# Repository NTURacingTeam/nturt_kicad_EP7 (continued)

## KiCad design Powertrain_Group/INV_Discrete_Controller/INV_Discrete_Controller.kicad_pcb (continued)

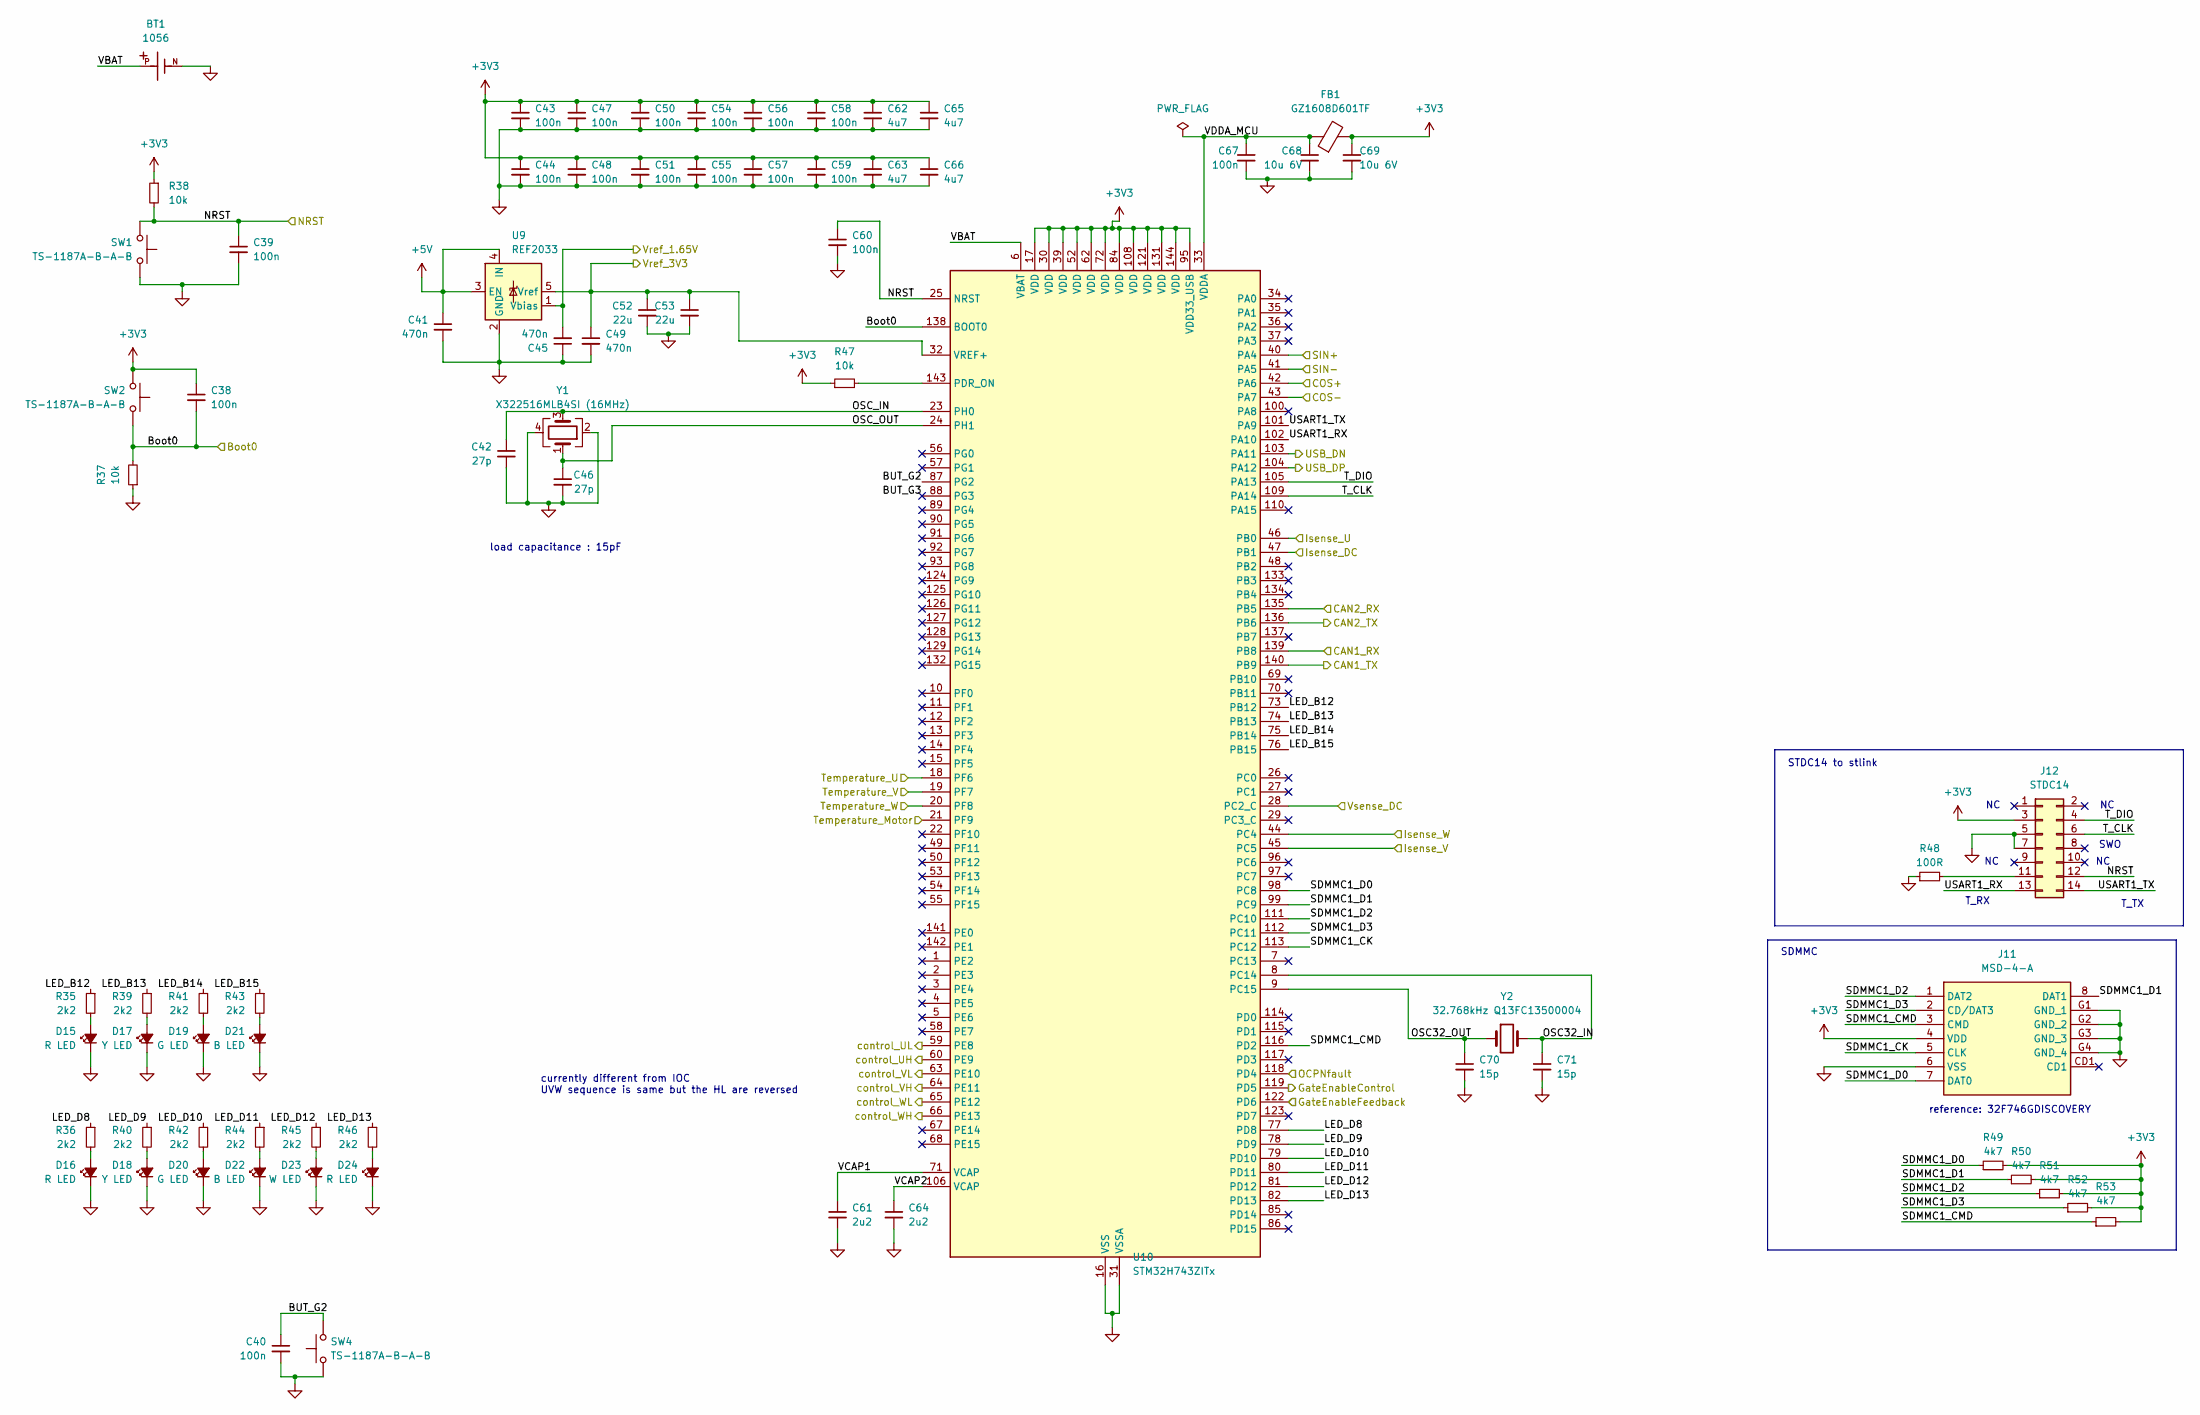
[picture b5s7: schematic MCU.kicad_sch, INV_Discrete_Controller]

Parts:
BT1: 1056; BAT_1056; PARTREV D
C38, C39, C40, C43, C44, C47, C48, C50, C51, C54, C55, C56, C57, C58, C59, C60, C67: 100n; C_0402_1005Metric
C41, C45, C49: 470n; C_0603_1608Metric
C42, C46: 27p; C_0402_1005Metric
C52, C53: 22u; C_0805_2012Metric
C61, C64: 2u2; C_0402_1005Metric
C62, C63, C65, C66: 4u7; C_0402_1005Metric
C68, C69: 10u 6V; C_0402_1005Metric
C70, C71: 15p; C_0402_1005Metric
D15, D16, D24: R LED; LED_0603_1608Metric
D17, D18: Y LED; LED_0603_1608Metric
D19, D20: G LED; LED_0603_1608Metric
D21, D22: B LED; LED_0603_1608Metric
D23: W LED; LED_0603_1608Metric
FB1: GZ1608D601TF; C_0603_1608Metric
J11: MSD-4-A; MSD4A; Mouser Part Number 179-MSD-4-A
J12: STDC14; box_header_14P_pitch1.27
R35, R36, R39, R40, R41, R42, R43, R44, R45, R46: 2k2; R_0402_1005Metric
R37, R38, R47: 10k; R_0402_1005Metric
R48: 100R; R_0402_1005Metric
R49, R50, R51, R52, R53: 4k7; R_0402_1005Metric
SW1, SW2, SW4: TS-1187A-B-A-B; SW_SPST_TL3342
U9: REF2033; SOT-23-5
U10: STM32H743ZITx; LQFP-144_20x20mm_P0.5mm
Y1: X322516MLB4SI (16MHz); Crystal_SMD_3225-4Pin_3.2x2.5mm
Y2: 32.768kHz Q13FC13500004; Crystal_SMD_3215-2Pin_3.2x1.5mm

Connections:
+3V3: C38.1, C43.1, C44.1, C47.1, C48.1, C50.1, C51.1, C54.1, C55.1, C56.1, C57.1, C58.1, C59.1, C62.1, C63.1, C65.1, C66.1, C69.1, FB1.2, J11.4 (VDD), J12.3, R38.1, R47.1, R49.2, R50.2, R51.2, R52.2, R53.2, SW2.2, U10.17 (VDD), U10.30 (VDD), U10.39 (VDD), U10.52 (VDD), U10.62 (VDD), U10.72 (VDD), U10.84 (VDD), U10.95 (VDD33_USB), U10.108 (VDD), U10.121 (VDD), U10.131 (VDD), U10.144 (VDD); also elsewhere on the board
+5V: C41.1, U9.3 (EN), U9.4 (IN); also elsewhere on the board
/EncoderDifVconverter/cos+3V3_out: U10.42 (PA6); also elsewhere on the board
/EncoderDifVconverter/cos-3V3_out: U10.43 (PA7); also elsewhere on the board
/EncoderDifVconverter/sin+3V3_out: U10.40 (PA4); also elsewhere on the board
/EncoderDifVconverter/sin-3V3_out: U10.41 (PA5); also elsewhere on the board
/GATE_EN: U10.122 (PD6); also elsewhere on the board
/GATE_ENC: U10.119 (PD5); also elsewhere on the board
/Isense&motT_OCP&OTP/Isense_DC: U10.47 (PB1); also elsewhere on the board
/Isense&motT_OCP&OTP/Isense_U: U10.46 (PB0); also elsewhere on the board
/Isense&motT_OCP&OTP/Isense_V: U10.45 (PC5); also elsewhere on the board
/Isense&motT_OCP&OTP/Isense_W: U10.44 (PC4); also elsewhere on the board
/Isense&motT_OCP&OTP/T_U: U10.18 (PF6); also elsewhere on the board
/Isense&motT_OCP&OTP/T_V: U10.19 (PF7); also elsewhere on the board
/Isense&motT_OCP&OTP/T_W: U10.20 (PF8); also elsewhere on the board
/Isense&motT_OCP&OTP/Temp_mot: U10.21 (PF9); also elsewhere on the board
/Isense&motT_OCP&OTP/Vref_1.65V: C45.2, U9.1 (Vbias); also elsewhere on the board
/Isense&motT_OCP&OTP/Vref_3V3: C49.1, C52.1, C53.1, U9.5 (Vref), U10.32 (VREF+)
/MCU/BUT_G2: C40.1, SW4.2, U10.87 (PG2)
/MCU/BUT_G3: U10.88 (PG3)
/MCU/Boot0: C38.2, R37.2, SW2.1, U10.138 (BOOT0); also elsewhere on the board
/MCU/CAN1_RX: U10.139 (PB8); also elsewhere on the board
/MCU/CAN1_TX: U10.140 (PB9); also elsewhere on the board
/MCU/CAN2_RX: U10.135 (PB5); also elsewhere on the board
/MCU/CAN2_TX: U10.136 (PB6); also elsewhere on the board
/MCU/LED_B12: R35.1, U10.73 (PB12)
/MCU/LED_B13: R39.1, U10.74 (PB13)
/MCU/LED_B14: R41.1, U10.75 (PB14)
/MCU/LED_B15: R43.1, U10.76 (PB15)
/MCU/LED_D8: R36.1, U10.77 (PD8)
/MCU/LED_D9: R40.1, U10.78 (PD9)
/MCU/LED_D10: R42.1, U10.79 (PD10)
/MCU/LED_D11: R44.1, U10.80 (PD11)
/MCU/LED_D12: R45.1, U10.81 (PD12)
/MCU/LED_D13: R46.1, U10.82 (PD13)
/MCU/NRST: C39.1, C60.1, J12.12, R38.2, SW1.2, U10.25 (NRST); also elsewhere on the board
/MCU/OSC32_IN: C71.1, U10.8 (PC14), Y2.2
/MCU/OSC32_OUT: C70.1, U10.9 (PC15), Y2.1
/MCU/OSC_IN: C42.1, U10.23 (PH0), Y1.3
/MCU/OSC_OUT: C46.1, U10.24 (PH1), Y1.1
/MCU/SDMMC1_CK: J11.5 (CLK), U10.113 (PC12)
/MCU/SDMMC1_CMD: J11.3 (CMD), R53.1, U10.116 (PD2)
/MCU/SDMMC1_D0: J11.7 (DAT0), R49.1, U10.98 (PC8)
/MCU/SDMMC1_D1: J11.8 (DAT1), R50.1, U10.99 (PC9)
/MCU/SDMMC1_D2: J11.1 (DAT2), R51.1, U10.111 (PC10)
/MCU/SDMMC1_D3: J11.2 (CD/DAT3), R52.1, U10.112 (PC11)
/MCU/T_CLK: J12.6, U10.109 (PA14)
/MCU/T_DIO: J12.4, U10.105 (PA13)
/MCU/USART1_RX: J12.13, U10.102 (PA10)
/MCU/USART1_TX: J12.14, U10.101 (PA9)
/MCU/USB_DN: U10.103 (PA11); also elsewhere on the board
/MCU/USB_DP: U10.104 (PA12); also elsewhere on the board
/MCU/VBAT: BT1.P, U10.6 (VBAT)
/MCU/VCAP1: C61.1, U10.71 (VCAP)
/MCU/VCAP2: C64.1, U10.106 (VCAP)
/MCU/VDDA_MCU: C67.1, C68.1, FB1.1, U10.33 (VDDA)
/MCU/Vsense_DC: U10.28 (PC2_C); also elsewhere on the board
/OCPFLTN: U10.118 (PD4); also elsewhere on the board
/UH: U10.60 (PE9); also elsewhere on the board
/UL: U10.59 (PE8); also elsewhere on the board
/VH: U10.64 (PE11); also elsewhere on the board
/VL: U10.63 (PE10); also elsewhere on the board
/WH: U10.66 (PE13); also elsewhere on the board
/WL: U10.65 (PE12); also elsewhere on the board
GND: BT1.N, C39.2, C40.2, C41.2, C42.2, C43.2, C44.2, C45.1, C46.2, C47.2, C48.2, C49.2, C50.2, C51.2, C52.2, C53.2, C54.2, C55.2, C56.2, C57.2, C58.2, C59.2, C60.2, C61.2, C62.2, C63.2, C64.2, C65.2, C66.2, C67.2, C68.2, C69.2, C70.2, C71.2, D15.1 (K), D16.1 (K), D17.1 (K), D18.1 (K), D19.1 (K), D20.1 (K), D21.1 (K), D22.1 (K), D23.1 (K), D24.1 (K), J11.6 (VSS), J11.G1 (GND_1), J11.G2 (GND_2), J11.G3 (GND_3), J11.G4 (GND_4), J12.5, J12.7, R37.1, R48.1, SW1.1, SW4.1, U9.2 (GND), U10.16 (VSS), U10.31 (VSSA), U10.38 (VSS), U10.51 (VSS), U10.61 (VSS), U10.83 (VSS), U10.94 (VSS), U10.107 (VSS), U10.120 (VSS), U10.130 (VSS), Y1.2, Y1.4; also elsewhere on the board
unnamed: D15.2 (A), R35.2
unnamed: D16.2 (A), R36.2
unnamed: D17.2 (A), R39.2
unnamed: D18.2 (A), R40.2
unnamed: D19.2 (A), R41.2
unnamed: D20.2 (A), R42.2
unnamed: D21.2 (A), R43.2
unnamed: D22.2 (A), R44.2
unnamed: D23.2 (A), R45.2
unnamed: D24.2 (A), R46.2
unnamed: J12.11, R48.2
unnamed: R47.2, U10.143 (PDR_ON)

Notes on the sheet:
reference: 32F746GDISCOVERY
load capacitance : 15pF
SDMMC
T_TX
SWO
STDC14 to stlink
currently different from IOC UVW sequence is same but the HL are reversed
T_RX

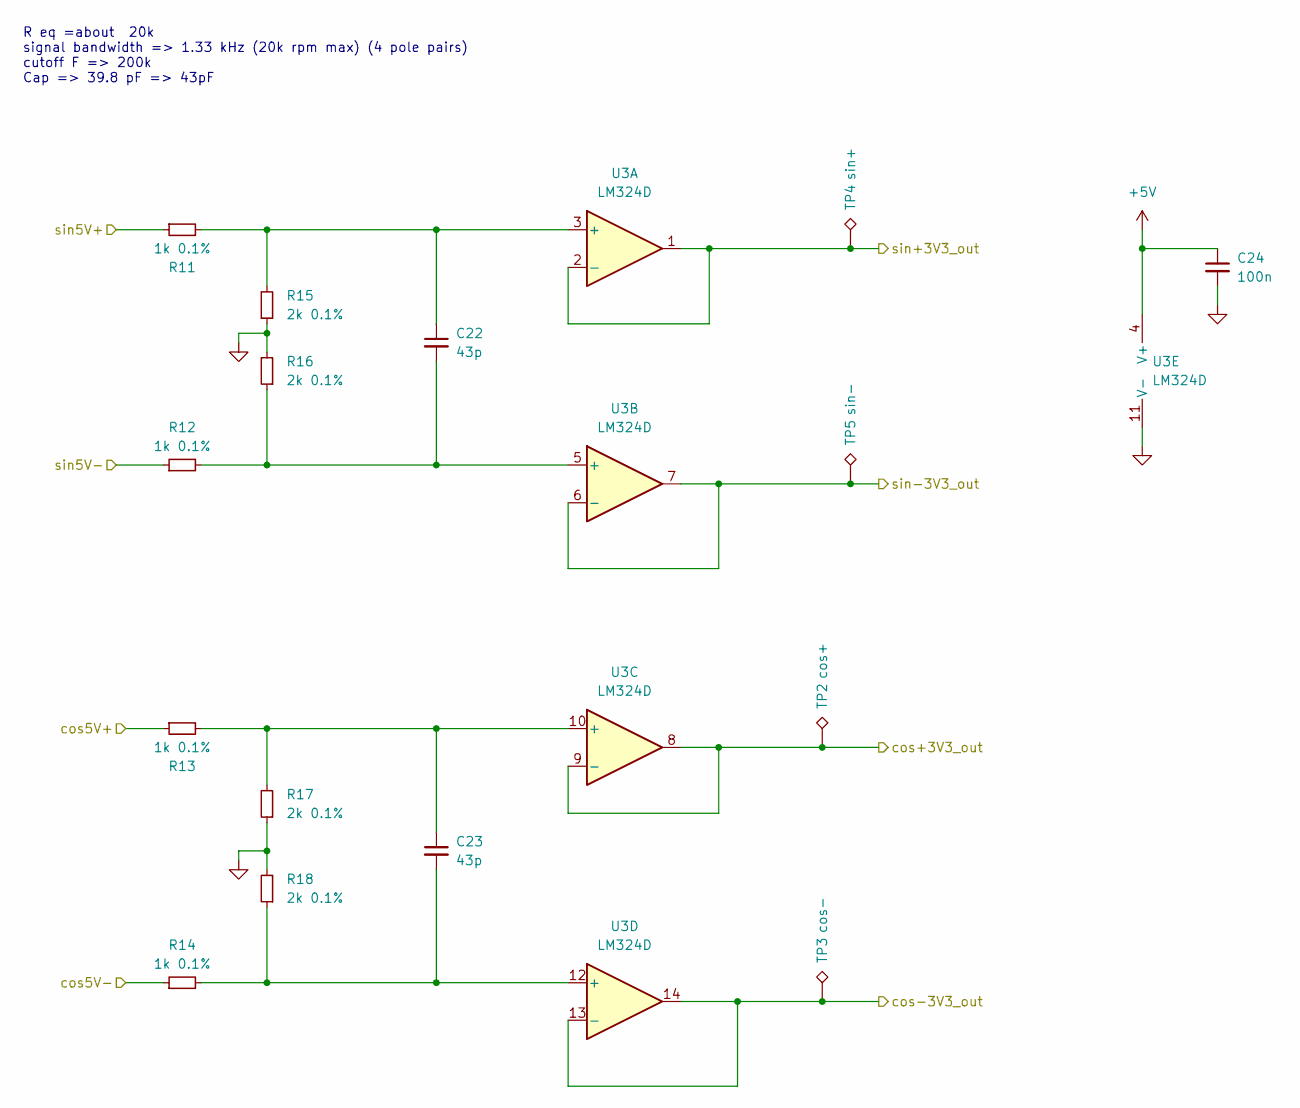
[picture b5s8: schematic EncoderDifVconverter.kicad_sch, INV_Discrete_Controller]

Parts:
C22, C23: 43p; C_0402_1005Metric
C24: 100n; C_0402_1005Metric
R11, R12, R13, R14: 1k 0.1%; R_0402_1005Metric
R15, R16, R17, R18: 2k 0.1%; R_0402_1005Metric
TP2: cos+; TestPoint_Pad_D1.0mm
TP3: cos-; TestPoint_Pad_D1.0mm
TP4: sin+; TestPoint_Pad_D1.0mm
TP5: sin-; TestPoint_Pad_D1.0mm
U3: LM324D; SOIC-14_3.9x8.7mm_P1.27mm

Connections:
+5V: C24.1, U3.4 (V+); also elsewhere on the board
/COS+: R13.1; also elsewhere on the board
/COS-: R14.1; also elsewhere on the board
/EncoderDifVconverter/cos+3V3_out: TP2.1, U3.8, U3.9 (-); also elsewhere on the board
/EncoderDifVconverter/cos-3V3_out: TP3.1, U3.13 (-), U3.14; also elsewhere on the board
/EncoderDifVconverter/sin+3V3_out: TP4.1, U3.1, U3.2 (-); also elsewhere on the board
/EncoderDifVconverter/sin-3V3_out: TP5.1, U3.6 (-), U3.7; also elsewhere on the board
/SIN+: R11.1; also elsewhere on the board
/SIN-: R12.1; also elsewhere on the board
GND: C24.2, R15.1, R16.2, R17.1, R18.2, U3.11 (V-); also elsewhere on the board
unnamed: C22.1, R11.2, R15.2, U3.3 (+)
unnamed: C22.2, R12.2, R16.1, U3.5 (+)
unnamed: C23.1, R13.2, R17.2, U3.10 (+)
unnamed: C23.2, R14.2, R18.1, U3.12 (+)

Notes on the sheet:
R eq =about 20k signal bandwidth => 1.33 kHz (20k rpm max) (4 pole pairs) cutoff F => 200k Cap => 39.8 pF => 43pF

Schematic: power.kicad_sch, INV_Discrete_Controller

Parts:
C1, C2, C6, C7, C10, C13, C16: 10u 35V; C_1206_3216Metric
C3: 100n; C_0603_1608Metric
C4, C18: 220u 35V; CP_Radial_D8.0mm_P3.80mm
C5: 10n; C_0603_1608Metric
C8, C9, C11, C12, C14, C15, C37, C108: 22u 25V; C_1206_3216Metric
C17: 330u 25V; CP_Radial_D8.0mm_P3.80mm
C19, C21: 47u 10V; C_1206_3216Metric
D3: SS54; D_SMA
D4, D8, D201, D202, D203, D204: WHITE LED; LED_0603_1608Metric
D5: 5.6V C19077441; D_SOD-323
D7: 27V C22375300; D_SOD-323
D9: WHITE 3V3; LED_0603_1608Metric
F1: 1A; Fuse_1206_3216Metric
F2: 0.5A; Fuse_1206_3216Metric
FL1: ACM70V-701-2PL-TL00; Common_Mode_Choke_4A_ACM70V7012PLTL00; Mouser Part Number 810-ACM70V7012PLTL00
J8, J9: LVBattery; JST_VH_B2P-VH_1x02_P3.96mm_Vertical
L1: 1u SRN3015-1R0Y; L_Wuerth_MAPI-3015
L2: 22uH 3.7A (SRR1260-220M); L_Bourns_SRR1260
R6: 47k; R_0603_1608Metric
R7: 15k; R_0603_1608Metric
R8, R10: 10k; R_0402_1005Metric
R9: 47k; R_0402_1005Metric
TP1: 5V_buck; TestPoint_Pad_D1.0mm
U1: TPS5430DDAR; TI_SO-PowerPAD-8_ThermalVias
U2: AMS1117-3.3; SOT-223-3_TabPin2

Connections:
+3V3: C21.1, D9.2 (A), U2.2 (VO); also elsewhere on the board
+5V: C19.1, C37.1, C108.1, D4.2 (A), D5.1 (K), D201.2 (A), D202.2 (A), D203.2 (A), D204.2 (A), F1.2, U2.3 (VI); also elsewhere on the board
+24V: C1.1, C2.1, C3.2, D7.1 (K), D8.2 (A), F2.2, U1.7 (VIN); also elsewhere on the board
/power/5V_buck: C8.1, C9.1, C11.1, C12.1, C14.1, C15.1, C17.1, F1.1, L2.2, R6.1, TP1.1
/power/5V_buck_FB: R6.2, R7.1, U1.4 (VSENSE)
/power/5V_buck_sw: C5.2, D3.1 (K), L2.1, U1.8 (PH)
/power/+24V_preCMfilter: FL1.1, J8.2, J9.2
/power/+24V_prefuse: C10.1, C13.1, C16.1, C18.1, F2.1, L1.2
/power/+24V_proCMfilter: C4.1, C6.1, C7.1, FL1.4, L1.1
GND: C1.2, C2.2, C3.1, C4.2, C6.2, C7.2, C8.2, C9.2, C10.2, C11.2, C12.2, C13.2, C14.2, C15.2, C16.2, C17.2, C18.2, C19.2, C21.2, C37.2, C108.2, D3.2 (A), D5.2 (A), D7.2 (A), FL1.3, R7.2, R8.2, R9.2, R10.2, U1.2 (NC), U1.3 (NC), U1.6 (GND), U1.9 (GNDPAD), U2.1 (GND); also elsewhere on the board
GNDPWR: FL1.2, J8.1, J9.1
unnamed: D8.1 (K), R9.1
unnamed: D9.1 (K), R10.1
unnamed: D4.1 (K), D201.1 (K), D202.1 (K), D203.1 (K), D204.1 (K), R8.1
unnamed: C5.1, U1.1 (BOOT)

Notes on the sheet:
5V buck
Main 24V in filter
1A max
3.3V LDO
FB Vref=1.221 R_FBB = 10k ~ 100k possible R_FBT, R_FBB 16,5.1 => 5.05 V 18, 5.6 => 5.146 V 7.5, 2.4 => 5.037 V 5.1, 1.6 => 5.113 V

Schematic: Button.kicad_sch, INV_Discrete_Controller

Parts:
C104: 1u; C_0402_1005Metric
C105: 1u; C_0805_2012Metric
D25: SM6T6V8A; D_SMB
J18: button; JST_PH_B2B-PH-K_1x02_P2.00mm_Vertical
R116: 1M; R_0402_1005Metric
R117, R118: 5k1; R_0402_1005Metric
R119: 10k; R_0402_1005Metric
U33: PC817; DIP-4_W7.62mm

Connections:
+3V3: R119.2; also elsewhere on the board
+5V: U33.1; also elsewhere on the board
/Peripherals/Button_NRST/out: C105.1, R119.1, U33.4; also elsewhere on the board
GND: C104.2, C105.2, D25.2 (A2), R117.1, U33.3; also elsewhere on the board
unnamed: C104.1, R118.1, U33.2
unnamed: D25.1 (A1), J18.1, R116.2, R117.2
unnamed: J18.2, R116.1, R118.2

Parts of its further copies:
C106: 1u; C_0402_1005Metric
C107: 1u; C_0805_2012Metric
D26: SM6T6V8A; D_SMB
J19: button; JST_PH_B2B-PH-K_1x02_P2.00mm_Vertical
R120: 1M; R_0402_1005Metric
R121, R122: 5k1; R_0402_1005Metric
R123: 10k; R_0402_1005Metric
U34: PC817; DIP-4_W7.62mm

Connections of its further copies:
+3V3: R123.2; also elsewhere on the board
+5V: U34.1; also elsewhere on the board
/Peripherals/Button_Boot0/out: C107.1, R123.1, U34.4; also elsewhere on the board
GND: C106.2, C107.2, D26.2 (A2), R121.1, U34.3; also elsewhere on the board
unnamed: C106.1, R122.1, U34.2
unnamed: D26.1 (A1), J19.1, R120.2, R121.2
unnamed: J19.2, R120.1, R122.2

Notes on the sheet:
Push Button -> Low

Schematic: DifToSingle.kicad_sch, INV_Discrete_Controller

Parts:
C20: ${Cap}; C_0402_1005Metric
C80, C81: 100n; C_0402_1005Metric
FB4: SDFL1608S100KTF 0603; C_0603_1608Metric
R68, R69: ${Res1}; R_0402_1005Metric
R71: ${Res2}; R_0402_1005Metric
U13: INA333AIDGK; VSSOP-8_3x3mm_P0.65mm

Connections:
+5V: C81.1, U13.7 (V+); also elsewhere on the board
/I_W+: R69.1; also elsewhere on the board
/I_W-: R68.1; also elsewhere on the board
/Isense&motT_OCP&OTP/Isense_W: U13.6; also elsewhere on the board
/Isense&motT_OCP&OTP/Vref_1.65V: FB4.2; also elsewhere on the board
GND: C80.2, C81.2, U13.4 (V-); also elsewhere on the board
unnamed: R71.1, U13.8 (Rg)
unnamed: R71.2, U13.1 (Rg)
unnamed: C20.1, R69.2, U13.3 (+)
unnamed: C20.2, R68.2, U13.2 (-)
unnamed: C80.1, FB4.1, U13.5 (Ref)

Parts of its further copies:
C82, C83, C84, C85: 100n; C_0402_1005Metric
FB5, FB6: SDFL1608S100KTF 0603; C_0603_1608Metric
U14, U15: INA333AIDGK; VSSOP-8_3x3mm_P0.65mm

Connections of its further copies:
+5V: C83.1, C85.1, U14.7 (V+), U15.7 (V+); also elsewhere on the board
/Isense&motT_OCP&OTP/Isense_U: U15.6; also elsewhere on the board
/Isense&motT_OCP&OTP/Isense_V: U14.6; also elsewhere on the board
/Isense&motT_OCP&OTP/Vref_1.65V: FB5.2, FB6.2; also elsewhere on the board
GND: C82.2, C83.2, C84.2, C85.2, U14.4 (V-), U15.4 (V-); also elsewhere on the board
unnamed 162: U14.8 (Rg); also elsewhere on the board
unnamed 163: U14.1 (Rg); also elsewhere on the board
unnamed 164: U15.8 (Rg); also elsewhere on the board
unnamed 165: U15.1 (Rg); also elsewhere on the board
unnamed 196: U14.3 (+); also elsewhere on the board
unnamed 197: U14.2 (-); also elsewhere on the board
unnamed: C82.1, FB5.1, U14.5 (Ref)
unnamed 199: U15.3 (+); also elsewhere on the board
unnamed 200: U15.2 (-); also elsewhere on the board
unnamed: C84.1, FB6.1, U15.5 (Ref)

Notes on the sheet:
Vout = (1+100k/${Res2}))* Vin = 1.1
R1 : ${Res1} R2 : ${Res2} gain = 1+100k/${Res2} = 1.2325

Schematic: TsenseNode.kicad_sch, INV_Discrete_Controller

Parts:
C95, C96: 1u; C_0603_1608Metric
R104, R105: 1K; R_0603_1608Metric

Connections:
+3V3: R104.1; also elsewhere on the board
/Isense&motT_OCP&OTP/T_U: C96.1, R105.2; also elsewhere on the board
/Isense&motT_OCP&OTP/TsenseNode/NTC_In_H: C95.1, R104.2, R105.1; also elsewhere on the board
GND: C95.2, C96.2; also elsewhere on the board

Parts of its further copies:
C97, C98, C99, C100: 1u; C_0603_1608Metric
R106, R107, R108, R109: 1K; R_0603_1608Metric

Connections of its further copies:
+3V3: R106.1, R108.1; also elsewhere on the board
/Isense&motT_OCP&OTP/T_V: C98.1, R107.2; also elsewhere on the board
/Isense&motT_OCP&OTP/T_W: C100.1, R109.2; also elsewhere on the board
/Isense&motT_OCP&OTP/TsenseNode1/NTC_In_H: C97.1, R106.2, R107.1; also elsewhere on the board
/Isense&motT_OCP&OTP/TsenseNode2/NTC_In_H: C99.1, R108.2, R109.1; also elsewhere on the board
GND: C97.2, C98.2, C99.2, C100.2; also elsewhere on the board

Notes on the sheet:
Vout = NTC/(R+NTC)*3V3

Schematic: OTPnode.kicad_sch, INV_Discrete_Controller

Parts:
C101: 100n; C_0402_1005Metric
FB12: GZ1608D601TF; C_0603_1608Metric
R110: 27k; R_0402_1005Metric
R111: 10k; R_0402_1005Metric
U30: LM393; SOIC-8_3.9x4.9mm_P1.27mm

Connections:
+3V3: FB12.1; also elsewhere on the board
/Isense&motT_OCP&OTP/OTPnode1/GateEnablePull: U30.1, U30.7; also elsewhere on the board
/Isense&motT_OCP&OTP/OTPnode1/filt3V3: C101.1, FB12.2, R110.1, U30.8 (V+)
/Isense&motT_OCP&OTP/OT_ref: U30.3 (+); also elsewhere on the board
/Isense&motT_OCP&OTP/T_V: U30.2 (-), U30.5 (+); also elsewhere on the board
GND: C101.2, R111.2, U30.4 (V-); also elsewhere on the board
unnamed: R110.2, R111.1, U30.6 (-)

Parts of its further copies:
C102, C103: 100n; C_0402_1005Metric
FB13, FB14: GZ1608D601TF; C_0603_1608Metric
R112, R114: 27k; R_0402_1005Metric
R113, R115: 10k; R_0402_1005Metric
U31, U32: LM393; SOIC-8_3.9x4.9mm_P1.27mm

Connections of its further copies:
+3V3: FB13.1, FB14.1; also elsewhere on the board
/Isense&motT_OCP&OTP/OTPnode2/GateEnablePull: U31.1, U31.7; also elsewhere on the board
/Isense&motT_OCP&OTP/OTPnode2/filt3V3: C102.1, FB13.2, R112.1, U31.8 (V+)
/Isense&motT_OCP&OTP/OTPnode/GateEnablePull: U32.1, U32.7; also elsewhere on the board
/Isense&motT_OCP&OTP/OT_ref: U31.3 (+), U32.3 (+); also elsewhere on the board
/Isense&motT_OCP&OTP/T_U: U32.2 (-), U32.5 (+); also elsewhere on the board
/Isense&motT_OCP&OTP/T_W: U31.2 (-), U31.5 (+); also elsewhere on the board
/Isense&motT_OCP&OTP/filt3V3: C103.1, FB14.2, R114.1, U32.8 (V+); also elsewhere on the board
GND: C102.2, C103.2, R113.2, R115.2, U31.4 (V-), U32.4 (V-); also elsewhere on the board
unnamed: R112.2, R113.1, U31.6 (-)
unnamed: R114.2, R115.1, U32.6 (-)

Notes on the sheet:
1 if V < 2.66 0 if V > 2.66
3.3v * 2.4 / 12.4 = 0.638v
1 if V > 0.638 0 if V < 0.638

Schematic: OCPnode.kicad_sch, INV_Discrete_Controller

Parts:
C86: 100n; C_0402_1005Metric
FB7: GZ1608D601TF; C_0603_1608Metric
R81, R84: ${Res2}; R_0402_1005Metric
R82, R83: ${Res1}; R_0402_1005Metric
U17: LM393; SOIC-8_3.9x4.9mm_P1.27mm

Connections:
+3V3: FB7.1; also elsewhere on the board
/Isense&motT_OCP&OTP/OCPnode1/GateEnablePull: U17.1, U17.7; also elsewhere on the board
/Isense&motT_OCP&OTP/OCPnode1/IsenseIn: U17.2 (-), U17.5 (+); also elsewhere on the board
/Isense&motT_OCP&OTP/OCPnode1/filt3V3: C86.1, FB7.2, R81.1, R83.1, U17.8 (V+)
GND: C86.2, R82.2, R84.2, U17.4 (V-); also elsewhere on the board
unnamed: R83.2, R84.1, U17.3 (+)
unnamed: R81.2, R82.1, U17.6 (-)

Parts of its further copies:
C87, C88: 100n; C_0402_1005Metric
FB8, FB9: GZ1608D601TF; C_0603_1608Metric
U18, U19: LM393; SOIC-8_3.9x4.9mm_P1.27mm

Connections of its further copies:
+3V3: FB8.1, FB9.1; also elsewhere on the board
/Isense&motT_OCP&OTP/OCPnode1/GateEnablePull: U18.1, U18.7, U19.1, U19.7; also elsewhere on the board
/Isense&motT_OCP&OTP/OCPnode2/IsenseIn: U18.2 (-), U18.5 (+); also elsewhere on the board
/Isense&motT_OCP&OTP/OCPnode2/filt3V3: C87.1, FB8.2, U18.8 (V+); also elsewhere on the board
/Isense&motT_OCP&OTP/OCPnode3/IsenseIn: U19.2 (-), U19.5 (+); also elsewhere on the board
/Isense&motT_OCP&OTP/OCPnode3/filt3V3: C88.1, FB9.2, U19.8 (V+); also elsewhere on the board
GND: C87.2, C88.2, U18.4 (V-), U19.4 (V-); also elsewhere on the board
unnamed 204: U18.3 (+); also elsewhere on the board
unnamed 205: U18.6 (-); also elsewhere on the board
unnamed 206: U19.3 (+); also elsewhere on the board
unnamed 207: U19.6 (-); also elsewhere on the board

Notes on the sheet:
1 if V < 2.66 0 if V > 2.66
3.3v * ${Res1} / ${Res1}+${Res2} = 0.191V
3.3v * ${Res2} / ${Res1}+${Res2} =3.109V
1 if (V > 0.637) & (V<2.66) 0 if (V > 2.66) || (V < 0.638) (pull down when overcurrent)
1 if V > 0.638 0 if V < 0.638

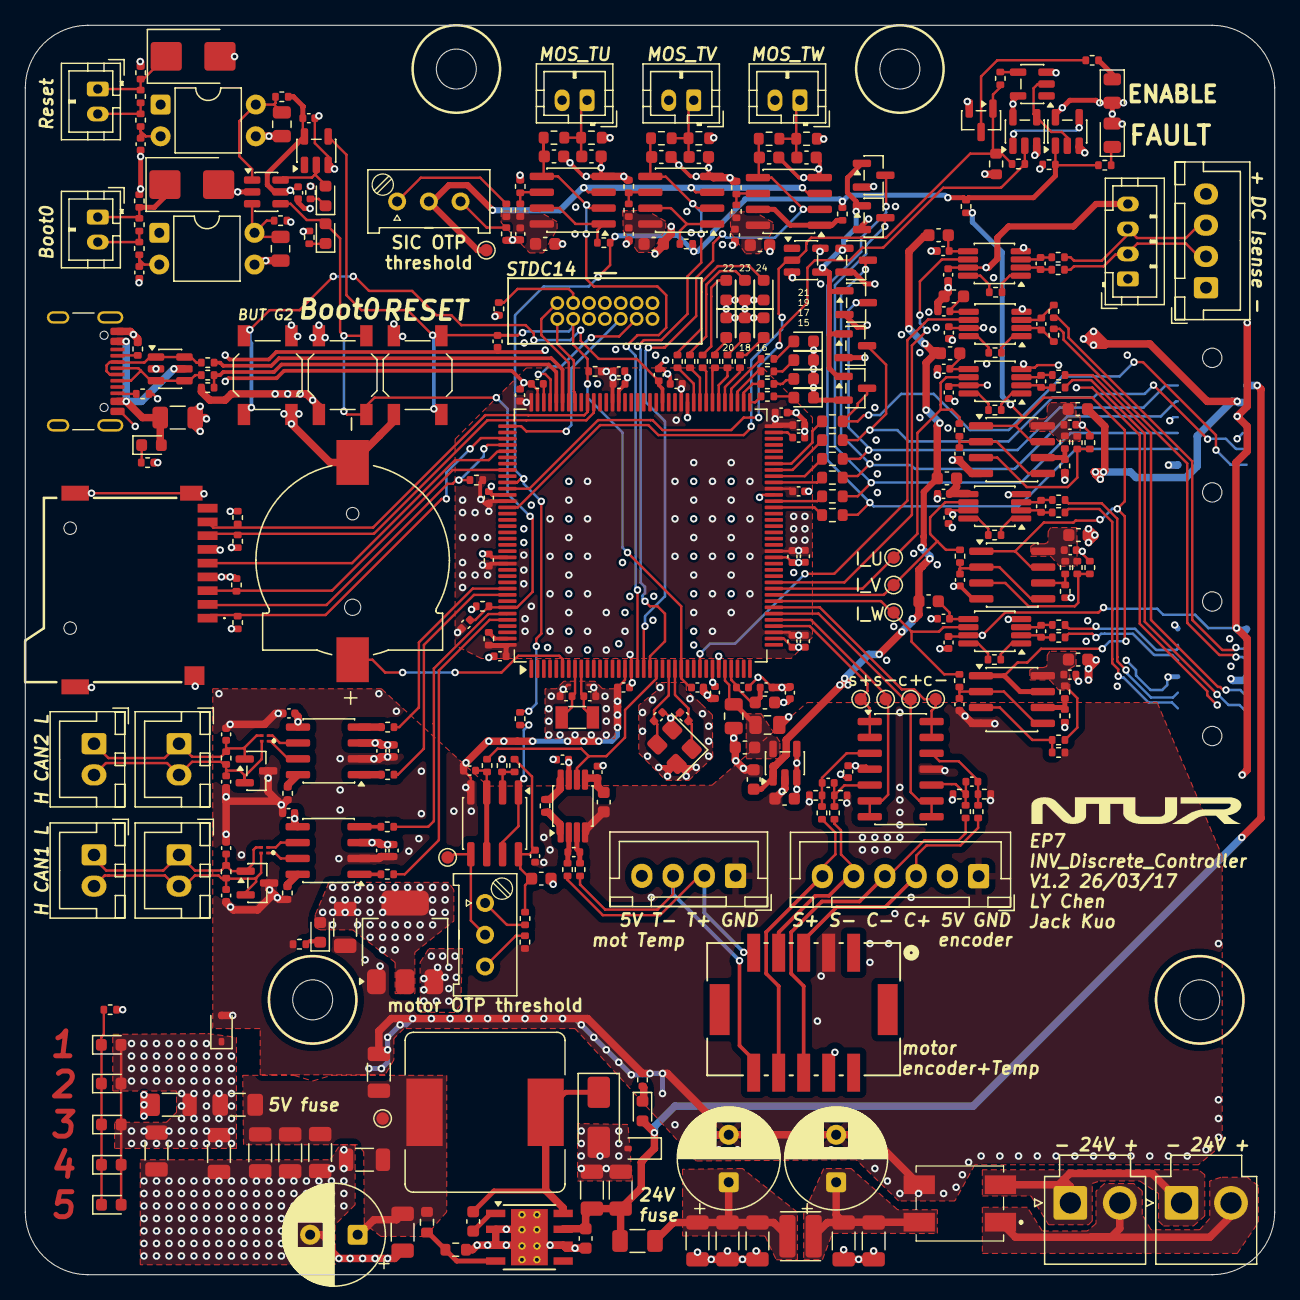
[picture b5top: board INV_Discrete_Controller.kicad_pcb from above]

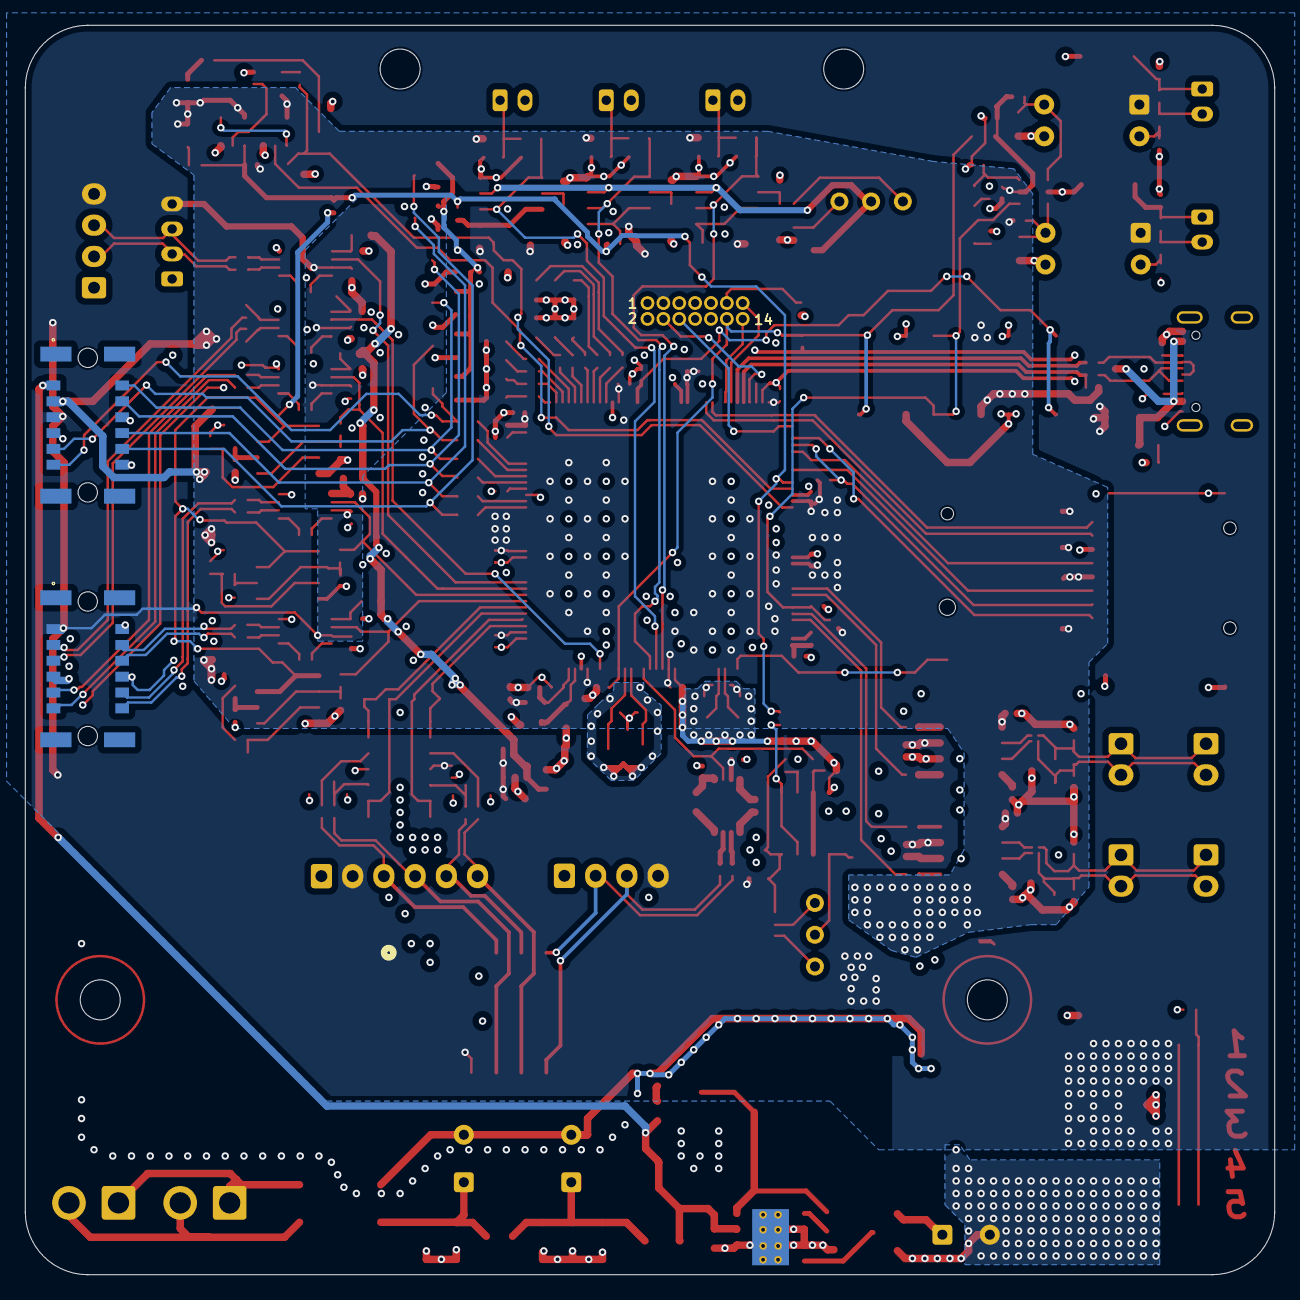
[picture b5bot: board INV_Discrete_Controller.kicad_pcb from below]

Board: 4 copper layers, 100.0 x 100.0 mm, 365 parts (2 on the bottom side), 217 nets.

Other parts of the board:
C89: 1u; C_0402_1005Metric
C92, C109, C110: 470p; C_0402_1005Metric
R72, R73, R76, R77, R101, R102: 150R; R_0402_1005Metric
R75, R79, R103: 1M; R_0402_1005Metric
R85, R88, R89, R92: 39k; R_0402_1005Metric
R86, R87, R90, R91: 2k4; R_0402_1005Metric
R95, R96: 10k; R_0402_1005Metric
R97: 100k; R_0402_1005Metric

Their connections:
/I_U+: R77.1; also elsewhere on the board
/I_U-: R76.1; also elsewhere on the board
/I_V+: R73.1; also elsewhere on the board
/I_V-: R72.1; also elsewhere on the board
/Isense&motT_OCP&OTP/OCPnode2/filt3V3: R85.1, R87.1; also elsewhere on the board
/Isense&motT_OCP&OTP/OCPnode3/filt3V3: R89.1, R91.1; also elsewhere on the board
/V_DC+: R102.1; also elsewhere on the board
/V_DC-: R101.1; also elsewhere on the board
/temp+: R96.1; also elsewhere on the board
/temp-: R95.1; also elsewhere on the board
GND: R86.2, R88.2, R90.2, R92.2; also elsewhere on the board
unnamed 162: R75.1; also elsewhere on the board
unnamed 163: R75.2; also elsewhere on the board
unnamed 164: R79.1; also elsewhere on the board
unnamed 165: R79.2; also elsewhere on the board
unnamed 166: R97.1; also elsewhere on the board
unnamed 167: R97.2; also elsewhere on the board
unnamed 168: R103.1; also elsewhere on the board
unnamed 169: R103.2; also elsewhere on the board
unnamed 196: C109.1, R73.2; also elsewhere on the board
unnamed 197: C109.2, R72.2; also elsewhere on the board
unnamed 199: C110.1, R77.2; also elsewhere on the board
unnamed 200: C110.2, R76.2; also elsewhere on the board
unnamed 204: R87.2, R88.1; also elsewhere on the board
unnamed 205: R85.2, R86.1; also elsewhere on the board
unnamed 206: R91.2, R92.1; also elsewhere on the board
unnamed 207: R89.2, R90.1; also elsewhere on the board
unnamed 209: C89.2, R96.2; also elsewhere on the board
unnamed 210: C89.1, R95.2; also elsewhere on the board
unnamed 212: C92.2, R102.2; also elsewhere on the board
unnamed 213: C92.1, R101.2; also elsewhere on the board

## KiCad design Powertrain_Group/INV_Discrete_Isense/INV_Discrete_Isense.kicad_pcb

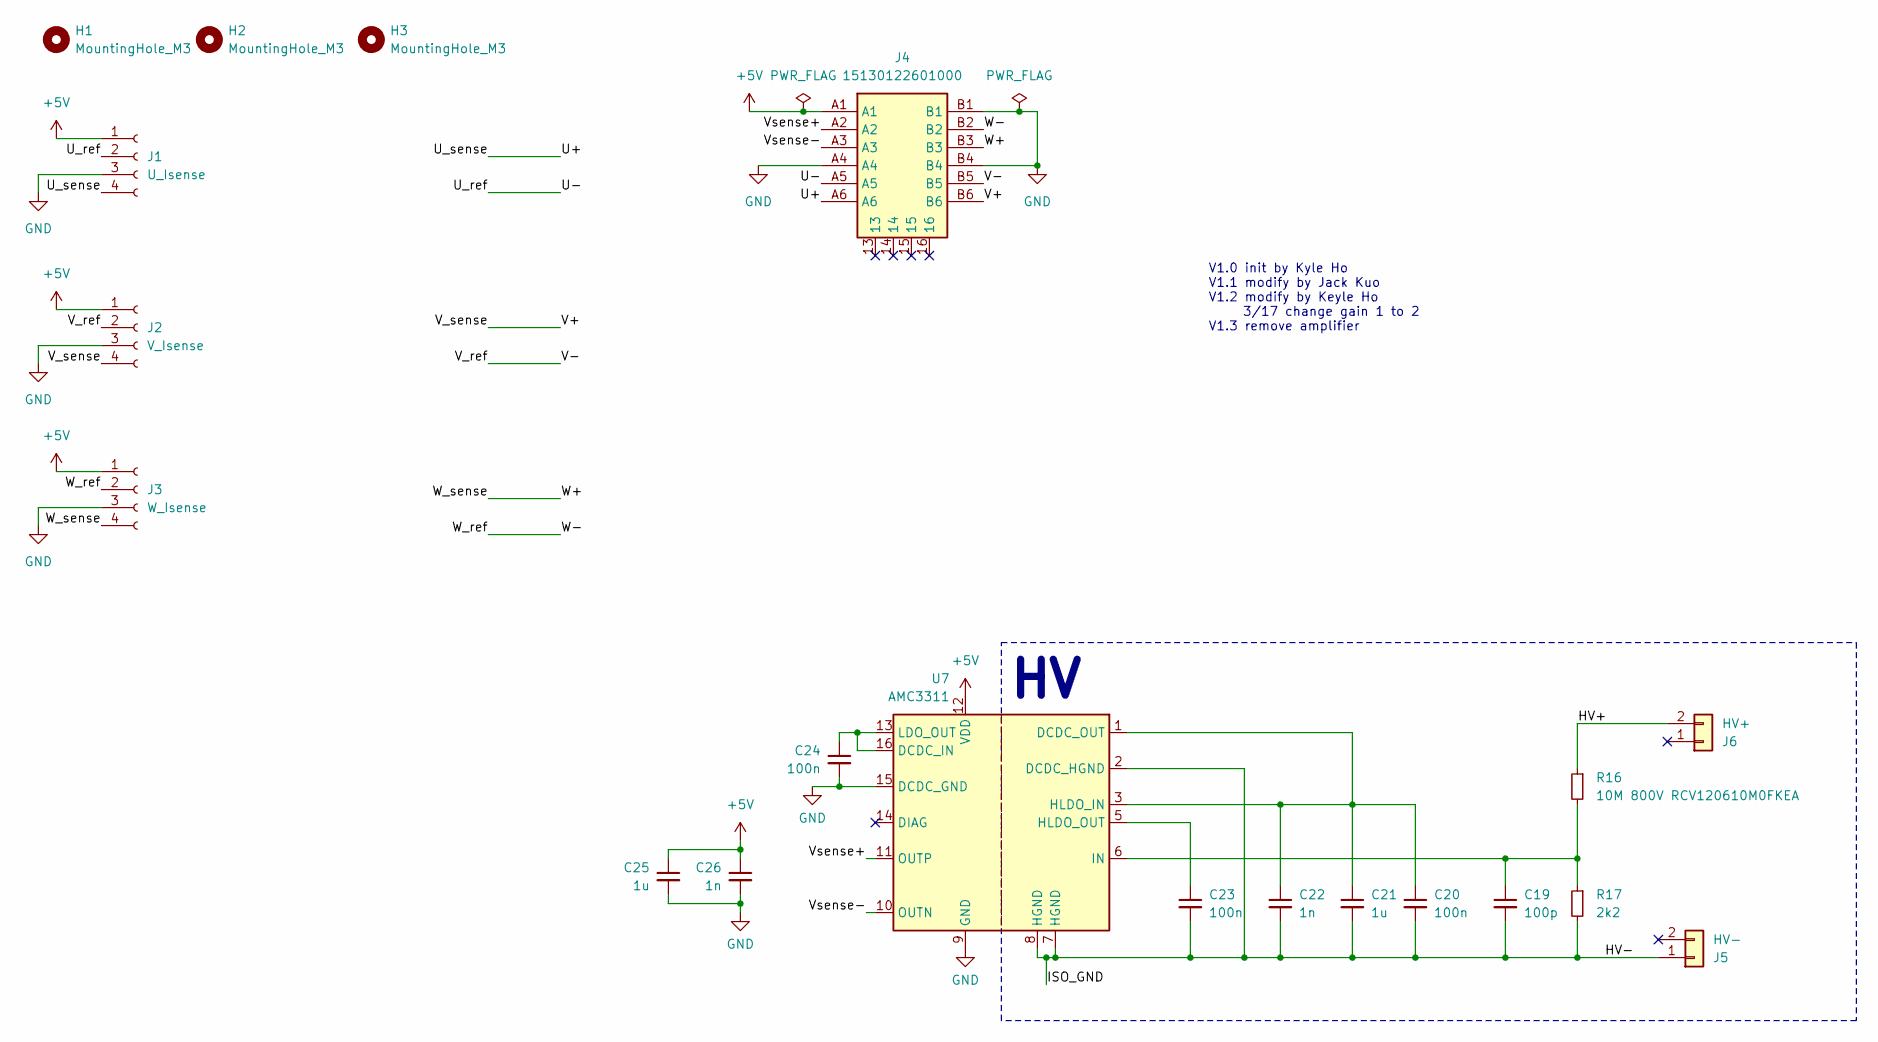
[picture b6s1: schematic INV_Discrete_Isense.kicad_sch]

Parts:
C19: 100p; C_0603_1608Metric
C20, C23, C24: 100n; C_0603_1608Metric
C21, C25: 1u; C_0603_1608Metric
C22, C26: 1n; C_0603_1608Metric
H1, H2, H3: MountingHole_M3; MountingHole_3.2mm_M3_ISO14580
J1: U_Isense; PinSocket_2x02_P2.54mm_Vertical
J2: V_Isense; PinSocket_2x02_P2.54mm_Vertical
J3: W_Isense; PinSocket_2x02_P2.54mm_Vertical
J4: 15130122601000; Harting_15130122601000; Mouser Part Number 617-15130122601000
J5: HV-; Hirose_DF1E2P25DS35; Mouser Part Number 798-DF1E-2P-2.5DS35
J6: HV+; Hirose_DF1E2P25DS35; Mouser Part Number 798-DF1E-2P-2.5DS35
R16: 10M 800V RCV120610M0FKEA; R_1206_3216Metric
R17: 2k2; R_0805_2012Metric_Pad1.20x1.40mm_HandSolder
U7: AMC3311; SOIC-16W_7.5x10.3mm_P1.27mm

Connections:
+5V: C25.1, C26.1, J1.1, J2.1, J3.1, J4.A1, U7.12 (VDD)
/HV+: J6.2, R16.1
/HV-: C19.2, C20.2, C21.2, C22.2, C23.2, J5.1, R17.2, U7.2 (DCDC_HGND), U7.7 (HGND), U7.8 (HGND)
/U+: J1.4, J4.A6
/U-: J1.2, J4.A5
/V+: J2.4, J4.B6
/V-: J2.2, J4.B5
/Vsense+: J4.A2, U7.11 (OUTP)
/Vsense-: J4.A3, U7.10 (OUTN)
/W+: J3.4, J4.B3
/W-: J3.2, J4.B2
GND: C24.2, C25.2, C26.2, J1.3, J2.3, J3.3, J4.A4, J4.B1, J4.B4, U7.9 (GND), U7.15 (DCDC_GND)
unnamed: C24.1, U7.13 (LDO_OUT), U7.16 (DCDC_IN)
unnamed: C20.1, C21.1, C22.1, U7.1 (DCDC_OUT), U7.3 (HLDO_IN)
unnamed: C23.1, U7.5 (HLDO_OUT)
unnamed: C19.1, R16.2, R17.1, U7.6 (IN)

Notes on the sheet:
V1.0 init by Kyle Ho V1.1 modify by Jack Kuo V1.2 modify by Keyle Ho 3/17 change gain 1 to 2 V1.3 remove amplifier
